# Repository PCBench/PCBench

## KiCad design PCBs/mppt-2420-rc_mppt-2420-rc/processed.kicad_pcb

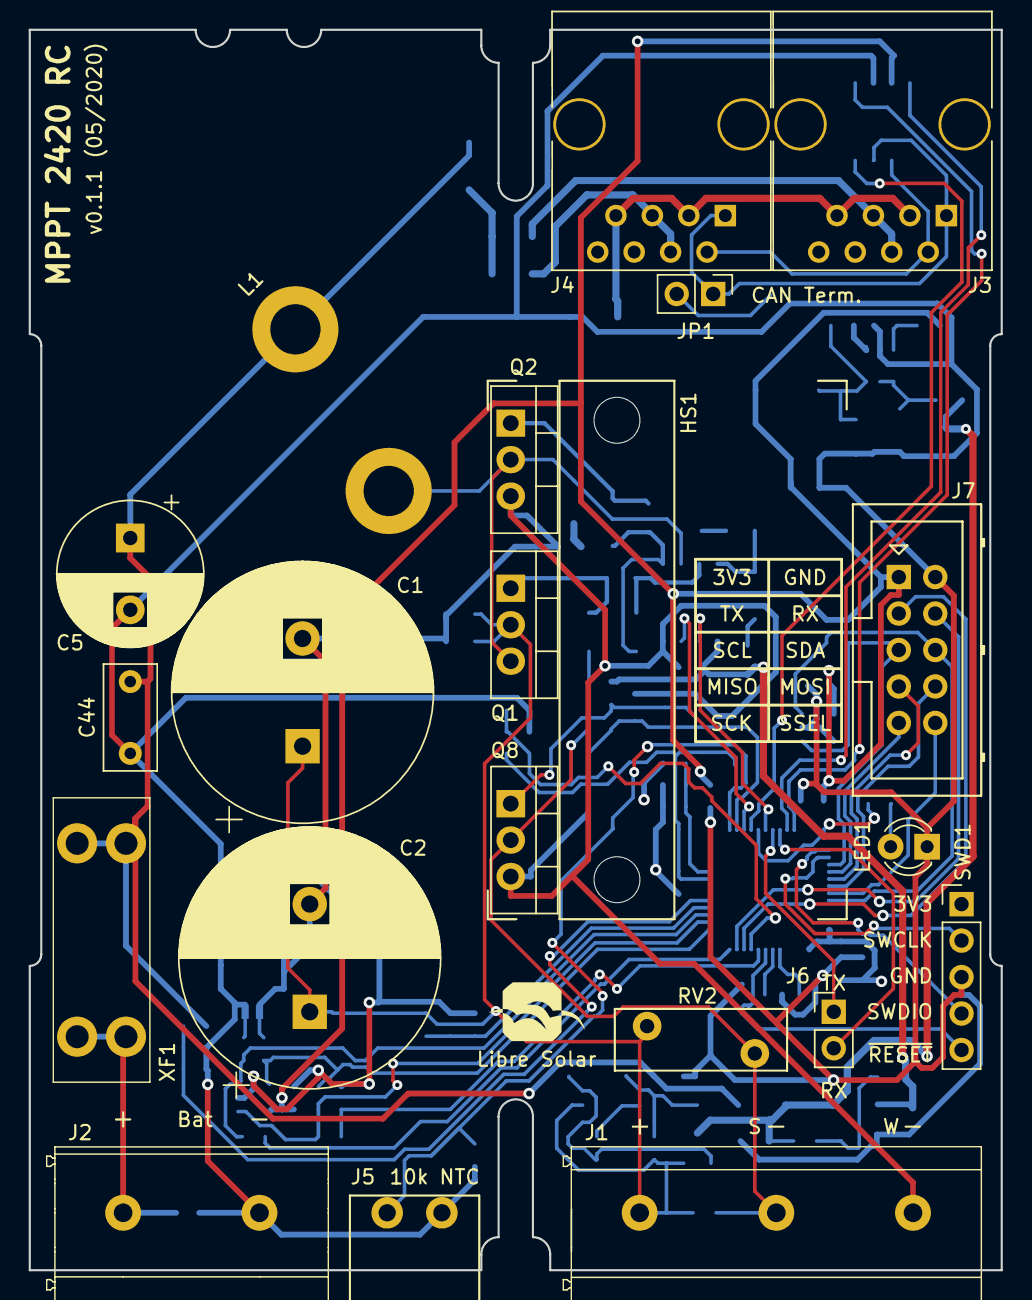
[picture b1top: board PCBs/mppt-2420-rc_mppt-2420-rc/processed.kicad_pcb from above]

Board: 4 copper layers, 67.7 x 86.4 mm, 120 parts (0 on the bottom side), 71 nets.

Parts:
C1, C2: 560µF; CP_Radial_D18.0mm_P7.50mm
C3, C18, C40: 1µF; C_0805_2012
C4: 100nF; C_0805_2012
C5: 820µF; CP_Radial_D10.0mm_P5.00mm
C6, C15: 1nF; C_0603_1608
C7, C9, C10, C11, C20, C22, C29, C30, C31, C32, C36, C48: 100nF; C_0603_1608
C8, C14, C16, C17, C34: 10nF; C_0603_1608
C12, C33, C39, C41, C49: 2.2µF; C_0603_1608
C19: 4.7µF; C_1210_3225
C21, C23: 10µF; C_0805_2012
C44: 0.22µF; C_Rect_L7.2mm_W3.5mm_P5.00mm_FKS2_FKP2_MKS2_MKP2
D1: SS16FP; D_PowerDI-123
D2, D3: NRVTS260ESFT1G; D_SOD-123
D5, D9, D11: 12V; D_SOT-23_ANK
D7, D14, D15: SS14FL; D_SOD-123
D8: 2.5V; D_SOD-123
D10, D16: 1N4148; D_SOD-123
F1: 25A; NULL
F2, F3: 600mA; Fuse_1206_3216Metric
FID1, FID2: Fiducial; Fiducial_0.7mm
HS1: Heatsink; Fischer_Elektronik_SK573_37,5
J1: MKDS 5/ 3-9,5; Phoenix_Contact_MKDS_5-3-9,5
J2: MKDS 5/ 2-9,5; Phoenix_Contact_MKDS_5-2-9,5
J3, J4: 8P8C; RJ45_8P8C
J5: Phoenix Contact MC 1,5; Phoenix_Contact_MC_1,5_2-G-3,81
J6: Conn_01x02; PinHeader_1x02_P2.54mm_Vertical
J7: UEXT; Box_Header_2x05x2.54mm_Straight
JP1: Jumper_NC_Small; PinHeader_1x02_P2.54mm_Vertical
L1: 33µH; L-FERYSTER-DTMSS-27
L2: 4.7µH; L_0805_2012Metric
L3: 47µH; Bourns_SRN6045TA
LED1: red; LED_D3.0mm
LOGO1: LIBRE_SOLAR; LIBRESOLAR_LOGO
LOGO2: OPEN_HARDWARE; OSHW-Logo_5.7x6mm_SilkScreen
NT1, NT2: Net-Tie_2; NetTie-2_SMD_Pad0.5mm
Q1, Q2, Q8: IPP045N10N3G; TO-220-3_Vertical
Q9: DMP10H4D2S; SOT-23
R1, R2, R3, R5: 3R3; R_0805_2012
R4: 2R2; R_1206_3216
R6: 2m; R_Bourns_CRE2512
R7, R24, R39, R41, R45, R64, R65, R66: 10k; R_0603_1608
R8, R10, R14, R20, R21: 2.2k; R_0603_1608
R9, R11: 68k; R_0603_1608
R12: 0R; R_0603_1608
R13, R17: 100k; R_0603_1608
R15, R42: 1k; R_0603_1608
R18: 5.6k; R_0603_1608
R22: 120R; R_1206_3216
R23, R60: 33k; R_0603_1608
R40: 100R; R_0603_1608
R56: 1M; R_0603_1608
RT1: 10k; R_0603_1608
RV2: 82V; RV_Disc_D12mm_W4.3mm_P7.5mm
SWD1: ST_Nucleo_SWD; PinHeader_1x05_P2.54mm_Vertical
T2, T6, T10: MMBT3904; SOT-23
TP4: 12V; TestPoint_Pad_D1.0mm
U1: LM5107; SOIC-8_3.9x4.9mm_Pitch1.27mm
U2: STM32G431CBTx; LQFP-48_7x7mm_P0.5mm
U3: TLV9001; SOT-23-5
U4: LMR16006X; SOT-23-6
U5: TCAN334; SOIC-8_3.9x4.9mm_Pitch1.27mm
U6: 24AA32; SOT-23-5
XF1: ATO blade fuse; Keystone-Fuse-3557-2
Y1: 8MHz; Resonator_Murata_CSTNE

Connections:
+3V3: C7.1, C11.1, C21.1, C22.1, C23.1, C30.1, C31.1, C32.1, C33.1, J7.1, L3.2, R20.2, R21.2, R23.1, R40.2, SWD1.1, U2.1, U2.48, U3.5, U5.3, U6.4
+12V: C12.1, C41.1, R3.2, R12.1, T10.2, TP4.1, U1.1
/BAT+: C8.1, J2.1, XF1.2
/CAN bus/CAN_GND: D3.2, J3.3, J3.7, J4.3, J4.7
/CAN bus/CAN_H: J3.1, J4.1, JP1.1, U5.7
/CAN bus/CAN_L: J3.2, J4.2, R22.2, U5.6
/CAN bus/CAN_RX: U2.33, U5.4
/CAN bus/CAN_STB: U2.28, U5.8
/CAN bus/CAN_TX: U2.34, U5.1
/CAN bus/CAN_V+1: F2.1, J3.4, J3.5
/CAN bus/CAN_V+2: F3.1, J4.4, J4.5
/DC/DC/HS_DRV: D14.1, R1.2, U1.7
/DC/DC/LS_DRV: D7.2, D15.1, R2.2, U1.5
/DC/DC/PWM_HS: U1.2, U2.30
/DC/DC/PWM_LS: U1.3, U2.27
/DC/DC/SHUNT_N: NT1.2, R10.1
/DC/DC/SHUNT_P: NT2.2, R8.1
/DC/DC/SW_NODE: C10.2, L1.1, Q1.3, Q2.2, R4.2, U1.6
/DCDC_HV+: C1.1, C2.1, C3.1, C4.1, C17.1, D11.1, J1.1, Q1.2, Q9.2, R13.1, R60.2, R65.2, RV2.1
/DCDC_HV-: C17.2, J1.2, Q8.2, R41.1, RV2.2
/MCU/ADC1_IN2: C9.1, R7.2, RT1.1, U2.9
/MCU/ADC1_IN11: D8.1, R41.2, T6.1, U2.26
/MCU/ADC1_IN12: C16.1, R17.2, R18.1, U2.17
/MCU/ADC1_IN15: C14.1, R13.2, R14.1, U2.16
/MCU/ADC2_IN1: C15.1, R15.2, U2.8
/MCU/DAC1: R9.1, U2.12
/MCU/I2C1_SCL: J7.5, R20.1, U2.39, U6.1
/MCU/I2C1_SDA: J7.6, R21.1, U2.44, U6.3
/MCU/LED_PWR: R42.2, U2.29
/MCU/OPAMP2_VINM: R10.2, R11.1, U2.13, U3.4
/MCU/OPAMP2_VINP: R8.2, R9.2, U2.15, U3.3
/MCU/OPAMP2_VOUT: R11.2, R15.1, U2.14, U3.1
/MCU/OSC_IN: U2.5, Y1.3
/MCU/OSC_OUT: U2.6, Y1.1
/MCU/SPI1_MISO: J7.7, U2.41
/MCU/SPI1_MOSI: J7.8, U2.42
/MCU/SPI1_SCK: J7.9, U2.40
/MCU/SPI1_SSEL: J7.10, U2.43
/MCU/SWCLK: SWD1.2, U2.38
/MCU/SWDIO: SWD1.4, U2.37
/MCU/TEMP_BAT: C36.1, J5.1, R39.2, U2.25
/MCU/USART1_RX: J6.2, U2.32
/MCU/USART1_TX: J6.1, U2.31
/MCU/USART2_RX: J7.4, U2.11
/MCU/USART2_TX: J7.3, U2.10
/MCU/~RESET: C29.1, SWD1.5, U2.7
/Power Supply/SMPS_SUPPLY: C18.1, C40.1, D10.1, L2.1, Q9.3, R64.2, T10.3
GND: C5.2, C7.2, C8.2, C9.2, C11.2, C14.2, C15.2, C16.2, C18.2, C19.2, C21.2, C22.2, C23.2, C29.2, C30.2, C31.2, C32.2, C33.2, C34.2, C36.2, C39.2, C40.2, C41.2, C44.1, C48.2, C49.2, D1.2, D3.1, D5.2, D9.2, J2.2, J5.2, J7.2, LED1.1, NT2.1, R6.1, R14.2, R18.2, R24.2, RT1.2, SWD1.3, U3.2, U4.2, U5.2, U6.2, U6.5, Y1.2
GNDPWR: C1.2, C2.2, C3.2, C4.2, C6.2, C12.2, D8.2, J1.3, NT1.1, Q2.3, Q8.3, R6.2, R56.2, T6.2, U1.4
unnamed: C6.1, R4.1
unnamed: C10.1, R5.2
unnamed: C19.1, L2.2, U4.4, U4.5
unnamed: C20.1, U4.1
unnamed: C20.2, D1.1, L3.1, U4.6
unnamed: D2.1, F2.2, F3.2
unnamed: D5.1, R64.1, T10.1
unnamed: D7.1, R12.2, R45.1
unnamed: D9.1, R60.1, T2.1
unnamed: D11.2, Q9.1, R65.1, R66.2
unnamed: D14.2, Q1.1, R1.1
unnamed: D15.2, Q2.1, R2.1
unnamed: D16.1, R5.1, U1.8
unnamed: D16.2, R3.1
unnamed: JP1.2, R22.1
unnamed: LED1.2, R42.1
unnamed: Q8.1, R45.2, R56.1, T6.3
unnamed: R23.2, R24.1, U4.3
unnamed: R66.1, T2.3
VBUS: C5.1, C44.2, D2.2, D10.2, L1.2, R17.1, T2.2, XF1.1
VDDA: C34.1, C39.1, R40.1, U2.21
VREF: C48.1, C49.1, R7.1, R39.1, U2.20

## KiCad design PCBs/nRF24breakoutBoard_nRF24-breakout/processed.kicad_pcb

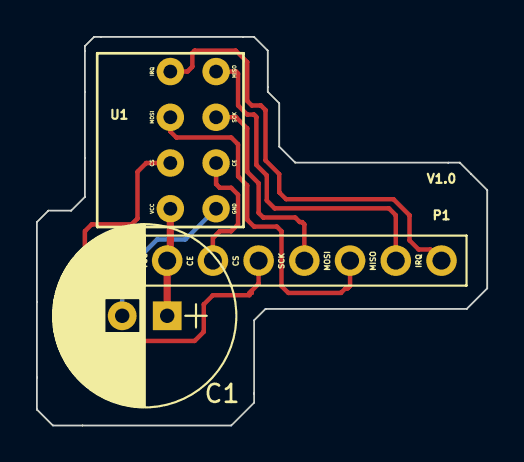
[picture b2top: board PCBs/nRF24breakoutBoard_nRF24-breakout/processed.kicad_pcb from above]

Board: 2 copper layers, 25.0 x 21.6 mm, 3 parts (0 on the bottom side), 8 nets.

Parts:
C1: 10uF; CP_Radial_D10.0mm_P2.50mm
P1: CONN_01X08; Pin_Header_Straight_1x08_Pitch2.54mm
U1: nRF24

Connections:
unnamed: C1.1, P1.2, U1.2
unnamed: C1.2, P1.1, U1.1
unnamed: P1.3, U1.3
unnamed: P1.4, U1.4
unnamed: P1.5, U1.5
unnamed: P1.6, U1.6
unnamed: P1.7, U1.7
unnamed: P1.8, U1.8

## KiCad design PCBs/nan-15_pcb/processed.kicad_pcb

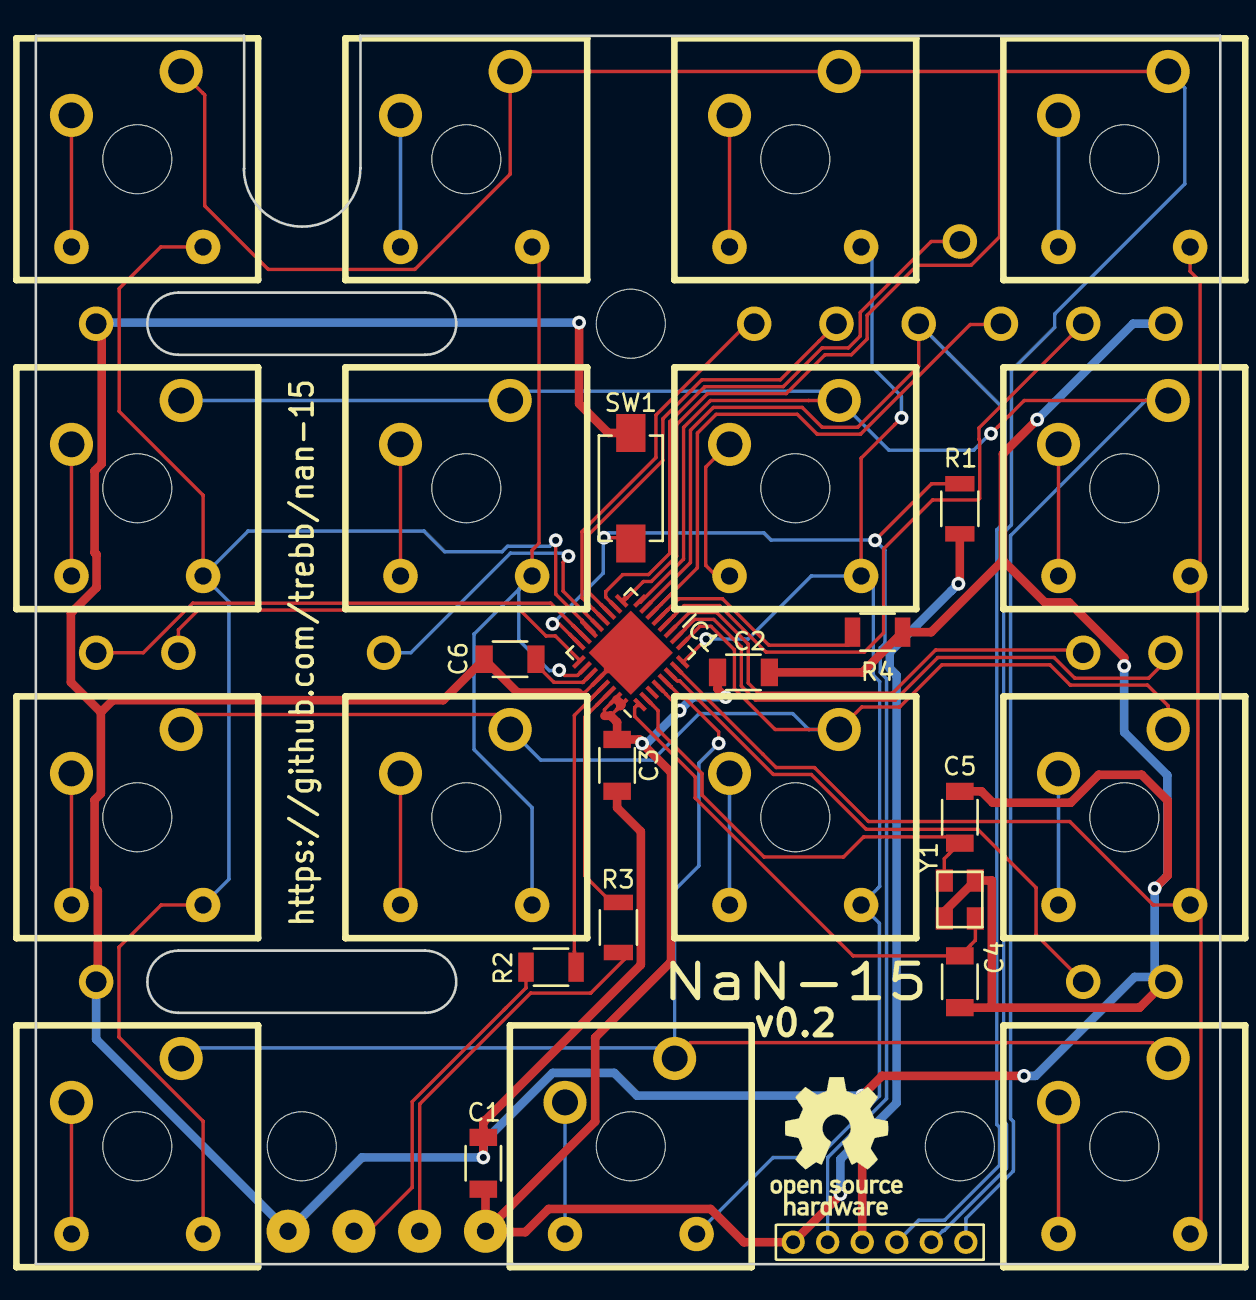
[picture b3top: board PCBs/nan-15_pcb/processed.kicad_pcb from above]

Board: 2 copper layers, 68.6 x 71.1 mm, 50 parts (1 on the bottom side), 46 nets.

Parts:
C1, C6: 1u; C_1206
C2, C3: 100n; C_1206
C4, C5: 18p; C_1206
HS1, HS2, HS3: HEATSINK; Plain_Hole_4mm
IC1: ATMEGA32U2; QFN-32-1EP_5x5mm_Pitch0.5mm
OSHW: OSHW-Logo_28.5x30mm_SilkScreen
P1: USB; SolderWirePad_4xInline_1mmDrill
P2: PRGM; Program_1x06
R1, R4: 10k; R_1206
R2, R3: 22; R_1206
SW1: SW_PUSH; button_3x6_smd
U00, U01, U02, U03, U10, U11, U12, U13, U20, U21, U22, U23, U30, U32, U33: MX-DI; MXDIODE
W0, W1, W2, W3, W4, W5, W6, W7, W8, W9, W10, W11, W50, W51, W52, W53: TEST_1P; SolderWirePad_2mm_1-2mmDrill_no_legend
Y1: MT 16MHz; crystal_MT_32x25

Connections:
/D+: IC1.29, R2.1
/D-: IC1.30, R3.1
/col0: IC1.22, U00.4, U10.4, U20.4, U30.4
/col1: IC1.26, U01.4, U11.4, U21.4
/col2: IC1.8, U02.4, U12.4, U22.4, U32.4
/col3: IC1.7, U03.4, U13.4, U23.4, U33.4
/led0: IC1.6, W0.1
/led1: IC1.10, W1.1
/led2: IC1.11, W2.1
/led3: IC1.12, W3.1
/led4: IC1.14, W4.1
/led5: IC1.15, P2.3, W5.1
/led6: IC1.18, W6.1
/led7: IC1.19, W7.1
/led8: IC1.20, W8.1
/led9: IC1.21, W9.1
/led10: IC1.25, W10.1
/led11: IC1.23, W11.1
/row0: IC1.17, P2.2, U00.2, U01.2, U02.2, U03.2
/row1: IC1.16, P2.1, U10.2, U11.2, U12.2, U13.2
/row2: IC1.9, U20.2, U21.2, U22.2, U23.2
/row3: IC1.5, U30.2, U32.2, U33.2
GND: C1.2, C2.2, C3.2, C4.2, C5.2, C6.1, IC1.28, IC1.33, P1.5, P2.4, R4.1, SW1.1, W50.1, W51.1, W52.1, W53.1, Y1.3
unnamed: C4.1, IC1.1
unnamed: C5.1, IC1.2
unnamed: C6.2, IC1.27
unnamed: IC1.13, R4.2
unnamed: IC1.24, P2.5, R1.2, SW1.2
unnamed: P1.2, R3.2
unnamed: P1.3, R2.2
unnamed: U00.1, U00.3
unnamed: U01.1, U01.3
unnamed: U02.1, U02.3
unnamed: U03.1, U03.3
unnamed: U10.1, U10.3
unnamed: U11.1, U11.3
unnamed: U12.1, U12.3
unnamed: U13.1, U13.3
unnamed: U20.1, U20.3
unnamed: U21.1, U21.3
unnamed: U22.1, U22.3
unnamed: U23.1, U23.3
unnamed: U30.1, U30.3
unnamed: U32.1, U32.3
unnamed: U33.1, U33.3
VCC: C1.1, C2.1, C3.1, IC1.4, IC1.31, IC1.32, P1.1, P2.6, R1.1

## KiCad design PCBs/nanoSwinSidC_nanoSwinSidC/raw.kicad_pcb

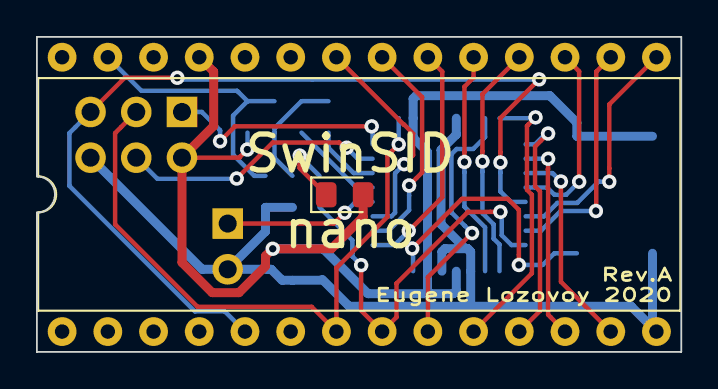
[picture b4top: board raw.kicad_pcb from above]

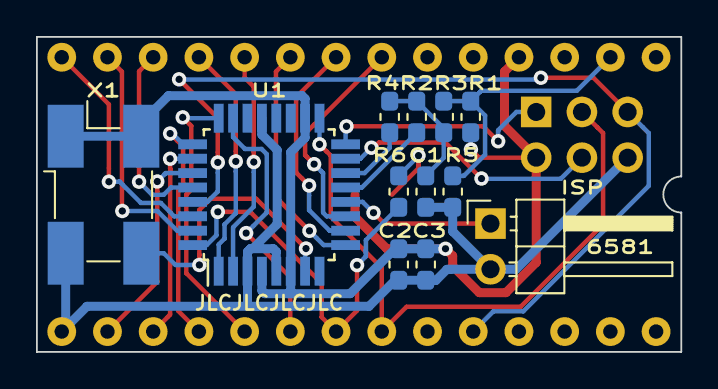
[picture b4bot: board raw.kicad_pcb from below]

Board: 2 copper layers, 35.8 x 17.5 mm, 15 parts (12 on the bottom side), 27 nets.

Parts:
C1: 470p; C_0603_1608Metric_Pad1.05x0.95mm_HandSolder
C2: 100n; C_0603_1608Metric_Pad1.05x0.95mm_HandSolder
C3: 10n; C_0603_1608Metric_Pad1.05x0.95mm_HandSolder
D1: LED; LED_0805_2012Metric_Pad1.15x1.40mm_HandSolder
J1: Conn_02x03_Odd_Even; PinHeader_2x03_P2.54mm_Vertical
J2: Conn_02x14_Counter_Clockwise; DIP-28_W15.24mm
JP1: Jumper; PinHeader_1x02_P2.54mm_Horizontal
R1: 4.7k; R_0603_1608Metric_Pad1.05x0.95mm_HandSolder
R2, R5, R6: 1k; R_0603_1608Metric_Pad1.05x0.95mm_HandSolder
R3: 2.2k; R_0603_1608Metric_Pad1.05x0.95mm_HandSolder
R4: 240k; R_0603_1608Metric_Pad1.05x0.95mm_HandSolder
U1: ATmega88PA-AU; TQFP-32_7x7mm_P0.8mm
X1: 32 MHz; Oscillator_SMD_EuroQuartz_XO91-4Pin_7.0x5.0mm_HandSoldering

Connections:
+5V: C2.1, C3.1, D1.2, J1.2, J2.25, R1.1, U1.4, U1.6, U1.18, X1.1, X1.4
A0: J2.9, U1.23
A1: J2.10, U1.24
A2: J2.11, U1.25
A3: J2.12, U1.26
A4: J2.13, U1.27
D0: J2.15, U1.30
D1: J2.16, U1.31
D2: J2.17, U1.28
D3: J2.18, U1.1
D4: J2.19, U1.2
D5: J2.20, U1.9
D6: J2.21, U1.10
D7: J2.22, U1.11
GND: C1.2, C2.2, C3.2, J1.6, J2.14, JP1.2, R5.2, U1.3, U1.5, U1.21, X1.2
MISO: J1.1, U1.16
MOSI: J1.4, U1.15
unnamed: C1.1, R2.1, R3.2, R4.1
unnamed: D1.1, R6.1
unnamed: JP1.1, U1.12
unnamed: R2.2, U1.13
unnamed: R4.2, U1.14
unnamed: U1.7, X1.3
SCK: J1.3, J2.7, U1.17
SND: J2.27, R1.2, R3.1, R5.1
nCS: J2.8, R6.2, U1.32
nRST: J1.5, J2.5, U1.29

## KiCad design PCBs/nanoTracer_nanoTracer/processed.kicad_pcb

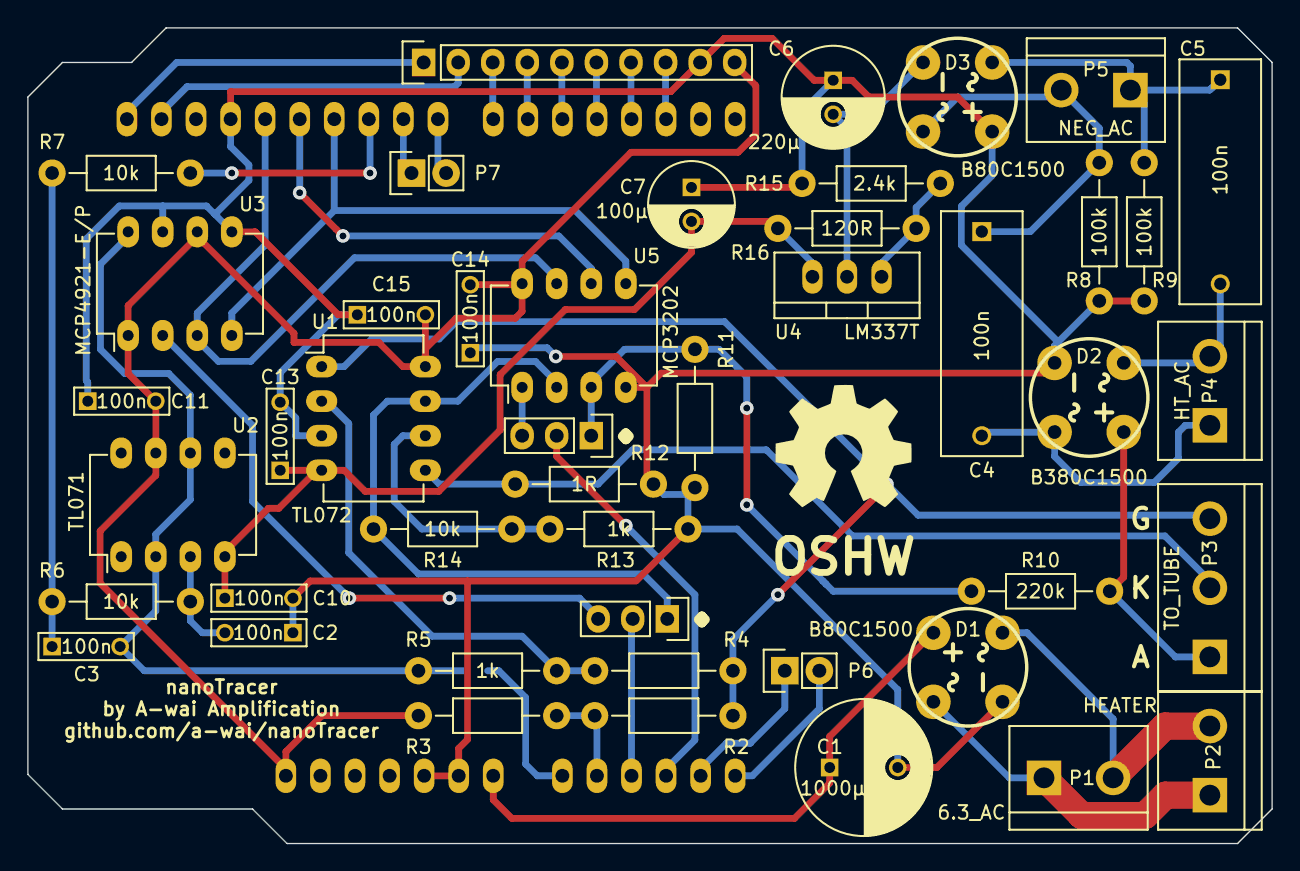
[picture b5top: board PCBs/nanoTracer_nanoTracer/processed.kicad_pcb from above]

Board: 2 copper layers, 91.4 x 59.9 mm, 48 parts (0 on the bottom side), 44 nets.

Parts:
C1: 1000µ; C_Radial_D10_L16_P5
C2, C3, C10, C11, C13, C14, C15: 100n; C_Rect_L7_W2_P5
C4, C5: 100n; C_Rect_L18_W6_H12_P15
C6: 220µ; C_Radial_D7.5_L11.2_P2.5
C7: 100µ; C_Radial_D6.3_L11.2_P2.5
D1, D3: B80C1500; bridge_wob
D2: B380C1500; bridge_wob
J1: SIL10; Pin_Header_Straight_1x10
JP1, JP2: JUMPER3; Pin_Header_Straight_1x03
JP3: JUMPER; SJ_OPEN
LOGO_OSHW_silkscreen_10mm: val**; LOGO_OSHW_silkscreen_10mm
P1: 6.3_AC; bornier2
P2: HEATER; bornier2
P3: TO_TUBE; bornier3
P4: HT_AC; bornier2
P5: NEG_AC; bornier2
P6, P7: CONN_2; Pin_Header_Straight_1x02
R2: R2; Resistor_Horizontal_RM10mm
R3: R3; Resistor_Horizontal_RM10mm
R4: R4; Resistor_Horizontal_RM10mm
R5, R13: 1k; Resistor_Horizontal_RM10mm
R6, R7, R14: 10k; Resistor_Horizontal_RM10mm
R8, R9: 100k; Resistor_Horizontal_RM10mm
R10: 220k; Resistor_Horizontal_RM10mm
R11: R11; Resistor_Horizontal_RM10mm
R12: 1R; Resistor_Horizontal_RM10mm
R15: 2.4k; Resistor_Horizontal_RM10mm
R16: 120R; Resistor_Horizontal_RM10mm
SHIELD1: ARDUINO_SHIELD
U1: TL072; DIP-8_W7.62mm_LongPads
U2: TL071; DIP-8_W7.62mm_LongPads
U3: MCP4921-E/P; DIP-8_W7.62mm_LongPads
U4: LM337T; TO-220_Neutral123_Vertical
U5: MCP3202; DIP-8_W7.62mm_LongPads

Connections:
/CS_ADC: JP1.3, U5.1
/CS_DAC: JP2.3, U3.2
/D8: P7.2, SHIELD1.8
/D9: P7.1, SHIELD1.9
/DAC_OUT: C3.2, JP3.1, R5.1, U2.2, U2.6, U3.8
/GRID: P3.3, R2.2, R4.2, U1.1
/IA: JP2.1, R14.1, U1.7, U5.2
/LCD_D4: J1.6, SHIELD1.4
/LCD_D5: J1.5, SHIELD1.5
/LCD_D6: J1.4, SHIELD1.6
/LCD_D7: J1.3, SHIELD1.7
/LCD_EN: J1.7, SHIELD1.3
/LCD_RS: J1.8, SHIELD1.2
/MISO: SHIELD1.12, U5.6
/MOSI: SHIELD1.11, U3.4, U5.5
/PWM_OUT: R7.1, SHIELD1.10
/SCK: SHIELD1.13, U3.3, U5.7
/SCL: J1.1, SHIELD1.SCL
/SDA: J1.2, SHIELD1.SDA
/UA: JP1.1, R10.2, R11.1, U5.3
/UG: R2.1, R3.2, SHIELD1.AD1
/UK: P3.2, R12.1, U1.5
/VIN: C1.1, D1.3, SHIELD1.V_IN
A+: D2.3, P3.1, R10.1
GND: C1.2, C2.1, C6.1, C7.1, C10.2, C11.1, C13.2, C14.1, C15.1, D1.1, D2.1, D3.3, J1.9, R8.1, R9.1, R11.2, R12.2, R13.1, R15.1, SHIELD1.GND1, SHIELD1.GND2, SHIELD1.GND3, U1.3, U3.5, U3.7, U5.4
unnamed: C2.2, R6.2, U2.3
unnamed: C3.1, R6.1, R7.2
unnamed: C4.1, D3.4, P5.2, R8.2
unnamed: C4.2, D2.4, P4.1
unnamed: C5.1, D3.2, P5.1, R9.2
unnamed: C5.2, D2.2, P4.2
unnamed: C6.2, D3.1, U4.2
unnamed: D1.2, P1.1, P2.1
unnamed: D1.4, P1.2, P2.2
unnamed: JP1.2, SHIELD1.AD3
unnamed: JP2.2, SHIELD1.AD2
unnamed: JP3.2, SHIELD1.AD0
unnamed: P6.1, SHIELD1.AD4
unnamed: P6.2, SHIELD1.AD5
unnamed: R4.1, R5.2, U1.2
unnamed: R13.2, R14.2, U1.6
unnamed: R15.2, R16.1, U4.1
VDD: C11.2, C14.2, C15.2, J1.10, R3.1, SHIELD1.IO_R, U1.8, U2.7, U3.1, U3.6, U5.8
VSS: C7.2, C10.1, C13.1, R16.2, U1.4, U2.4, U4.3

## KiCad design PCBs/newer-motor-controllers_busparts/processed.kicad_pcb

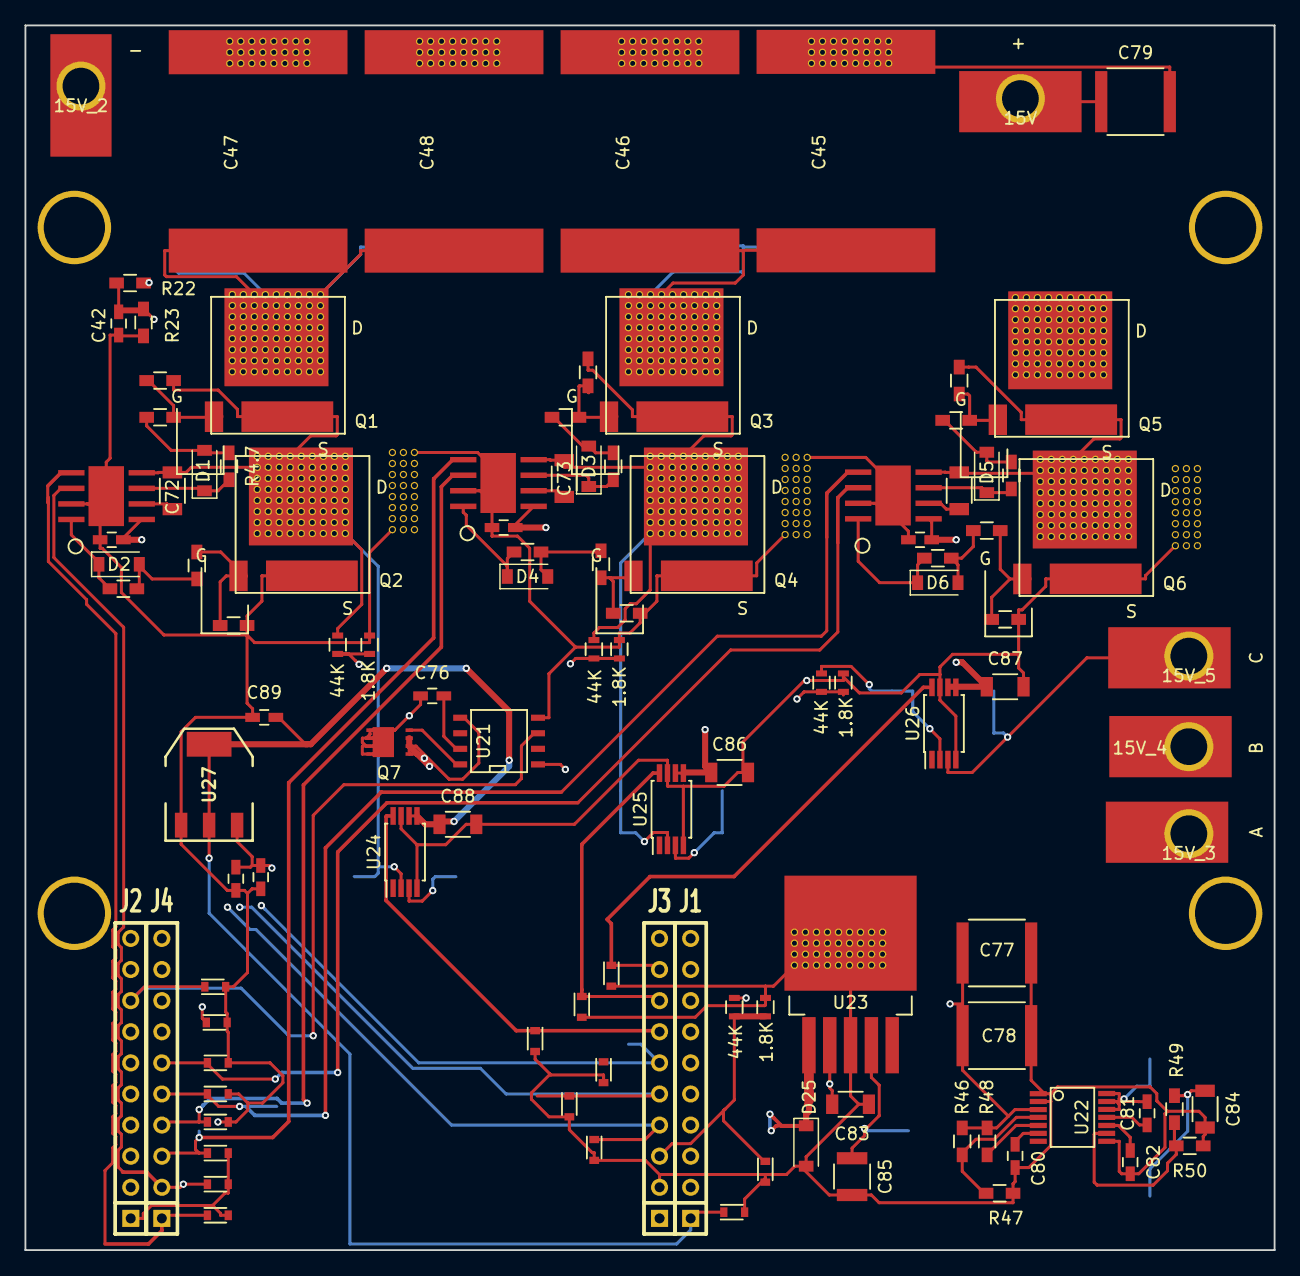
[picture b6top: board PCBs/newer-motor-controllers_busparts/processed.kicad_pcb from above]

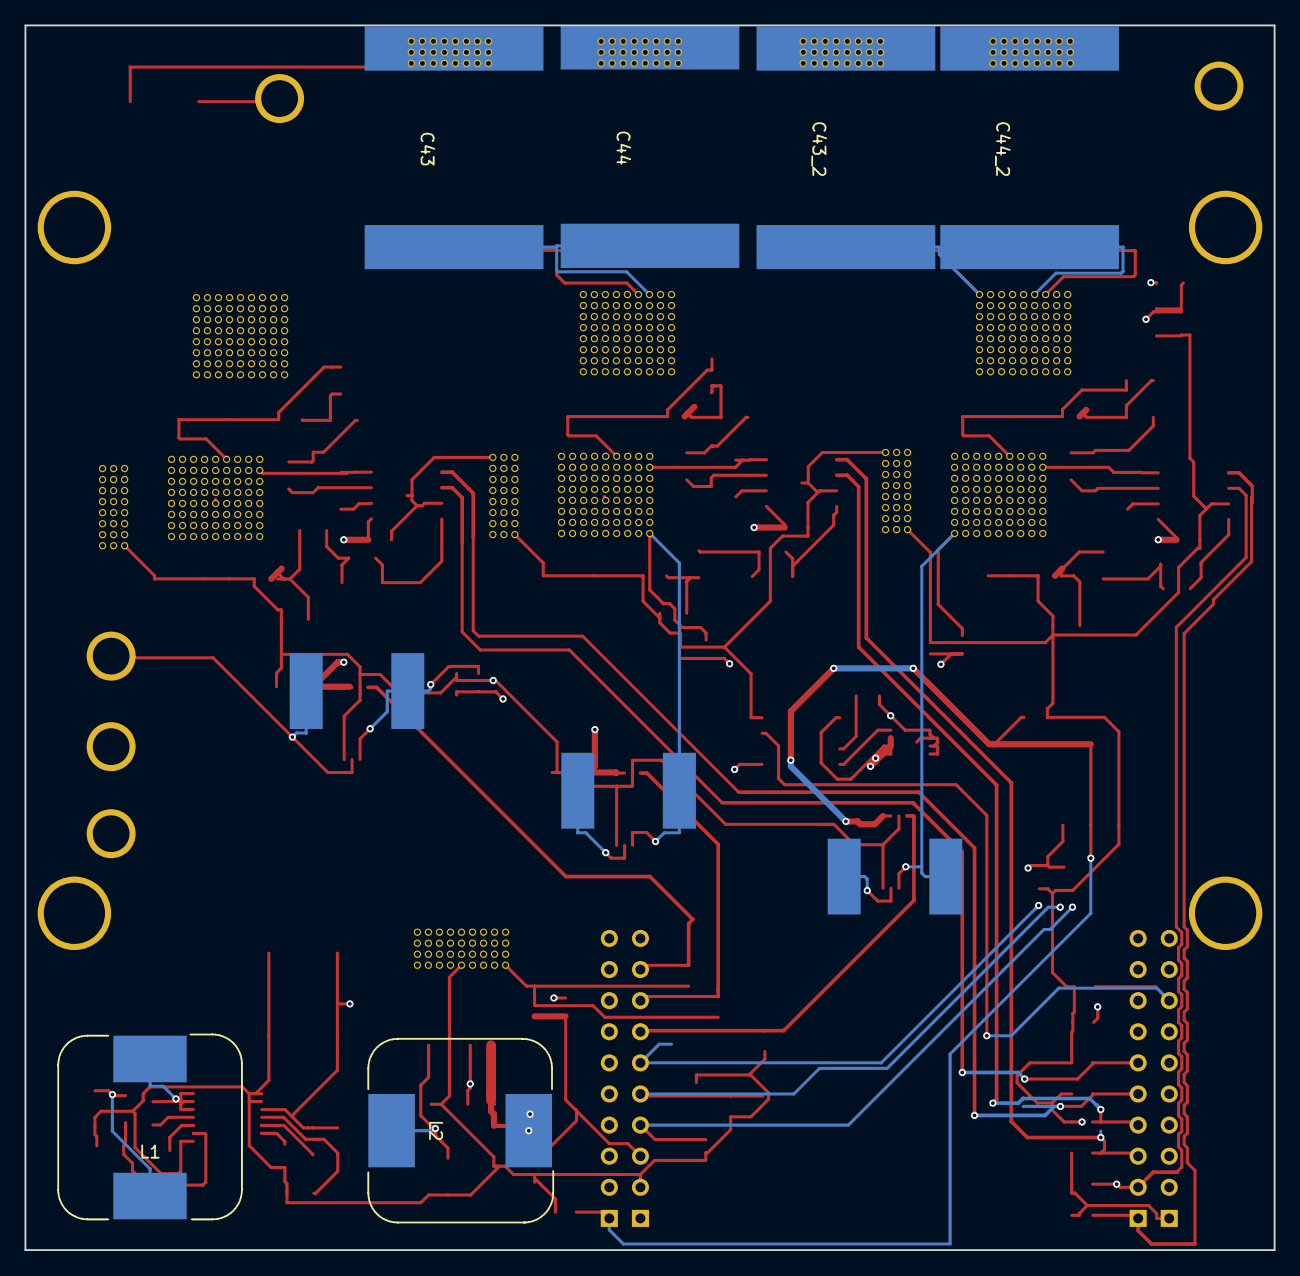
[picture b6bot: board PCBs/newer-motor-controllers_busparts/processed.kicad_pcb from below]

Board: 4 copper layers, 102.0 x 100.0 mm, 123 parts (9 on the bottom side), 58 nets.

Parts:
10k1, 10k2, 10k3, 10k4, 10k5, 10k6: R_Small; R_0603_HandSoldering
15V, 15V_2, 15V_3, 15V_4, 15V_5: via
+: V+; SolderWirePad_single_SMD_5x10mm
-: V-; SolderWirePad_single_SMD_5x10mm
A: motor_A; SolderWirePad_single_SMD_5x10mm
B: motor_B; SolderWirePad_single_SMD_5x10mm
C: motor_C; SolderWirePad_single_SMD_5x10mm
C42: 2.2uf; C_0603_HandSoldering
C43, C43_2, C44, C44_2, C45, C46, C47, C48: 4.7uf; cap_6065
C69, C70, C71, C82, C89: 1uf; C_0603_HandSoldering
C72, C73, C74, C86, C87, C88: 0.1uf; C_1206
C75: 0.1uf; C_0603_HandSoldering
C76: 10pf; C_0603_HandSoldering
C77, C78, C79: 1uf 250V; C_2220
C80: 22nf; C_0603_HandSoldering
C81: 10nf; C_0603_HandSoldering
C83, C84: 10uf; C_1206
C85: 100uf; C_1210
C90: 10uf; C_0603_HandSoldering
D1, D2, D3, D4, D5, D6: D_Schottky_Small; SOD-123
D8, D9, D10, D11, D12, D13, D14, D15, D16, D17, D18, D19, D20, D21, D22, D23: TVS; D_0603
D25: D_Schottky; SOD-123
J1: Ti_Booster_40_J1; SIL-10J1
J2: Ti_Booster_40_J2; SIL-10J2
J3: Ti_Booster_40_J3; SIL-10J3
J4: Ti_Booster_40_J4; SIL-10J4
L1, L2: INDUCTOR; MSS1583-154KED
Q1, Q2, Q3, Q4, Q5, Q6: FDMT-800; P-PG-HSOF-08
Q7: Q_NMOS_DSG; VSONP-8
R4.1, R4.2, R4.3, R4.4, R4.5, R4.7: R_Small; R_0603_HandSoldering
R22: NTC 10k; R_0603_HandSoldering
R23: 10k; R_0603_HandSoldering
R40, R41, R42, R42_2: 1.8K; R_0603
R43, R44, R45, R45_2: 44K; R_0603
R46: 75k; R_0603_HandSoldering
R47: 4.42k; R_0603_HandSoldering
R48: 499k; R_0603_HandSoldering
R49: 13k; R_0603_HandSoldering
R50: 2k; R_0603_HandSoldering
R51, R52, R53: 0.001R; SHUNT_CSS2H-3920
U18, U19, U20: UCC27210; SO_PowerPAD-8
U21: Si8751; SOIC-8-N
U22: LM5161; SSOP-14
U23: LM2595; TO-263-5Lead
U24, U25, U26: INA240; TSSOP-8_4.4x3mm_Pitch0.65mm
U27: NCP1117ST33T3G; SOT-223
ferrite1, ferrite2, ferrite3, ferrite4, ferrite5, ferrite6: R_Small; R_0603_HandSoldering

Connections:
+5V: C75.1, C85.1, C90.1, J3.1, L2.2, U21.1, U23.4, U27.3
+15V: C76.1, C83.1, C84.1, L1.2, Q7.1, R49.1, U23.2
/Ti_120vgate/vsense_a: D12.1, J3.4, R40.2, R43.2
/Ti_120vgate/vsense_b: D13.1, J3.5, R41.2, R44.2
/Ti_120vgate/vsense_c: J3.6, R42.2, R45.2
/VBUS: 15V.1, +.1, C43.2, C43_2.2, C44.2, C44_2.2, C45.2, C46.2, C47.2, C48.2, C77.1, C78.1, C79.1, Q1.1, Q3.1, Q5.1, R45_2.1, R46.1, R48.2, U22.3
/connector/CurrentA: D15.1, J3.7, U24.8
/connector/CurrentB: D16.1, J3.8, U25.8
/connector/CurrentC: D17.1, J3.9, U26.8
/connector/EN_GATE: D10.1, J2.8, U21.3
/connector/PWM_H1: D18.1, J4.1, U18.5
/connector/PWM_H2: D20.1, J4.3, U19.5
/connector/PWM_H3: D22.1, J4.5, U20.5
/connector/PWM_L1: D19.1, J4.2, U18.6
/connector/PWM_L2: D21.1, J4.4, U19.6
/connector/PWM_L3: D23.1, J4.6, U20.6
/connector/TEMP: C42.1, D8.1, J2.3, R22.2, R23.1
/connector/VBUS_sense: D11.1, J3.3, R42_2.2, R45_2.2
/current_sense_80v/PHASE_1: 15V_3.1, A.1, R53.1, U24.3
/current_sense_80v/PHASE_2: 15V_4.1, B.1, R52.1, U25.3
/current_sense_80v/PHASE_3: 15V_5.1, C.1, R51.1, U26.3
/mosfet/H1: D1.1, R4.7.2, U18.3
/mosfet/H2: D3.1, R4.2.2, U19.3
/mosfet/H3: D5.1, R4.4.2, U20.3
/mosfet/L1: D2.1, R4.1.2, U18.8
/mosfet/L2: D4.1, R4.3.2, U19.8
/mosfet/L3: D6.1, R4.5.2, U20.8
/mosfet/phase_a_in: 10k1.2, C72.1, Q1.2, Q2.1, R43.1, R53.2, U18.4, U24.2
/mosfet/phase_b_in: 10k3.2, C73.1, Q3.2, Q4.1, R44.1, R52.2, U19.4, U25.2
/mosfet/phase_c_in: 10k5.2, C74.1, Q5.2, Q6.1, R45.1, R51.2, U20.4, U26.2
GND: 10k2.2, 10k4.2, 10k6.2, 15V_2.1, -.1, C42.2, C43.1, C43_2.1, C44.1, C44_2.1, C45.1, C46.1, C47.1, C48.1, C69.2, C70.2, C71.2, C75.2, C77.2, C78.2, C79.2, C80.2, C82.2, C83.2, C84.2, C85.2, C86.2, C87.2, C88.2, C89.2, C90.2, D8.2, D9.2, D10.2, D11.2, D12.2, D13.2, D14.2, D15.2, D16.2, D17.2, D18.2, D19.2, D20.2, D21.2, D22.2, D23.2, D25.2, J2.1, J3.2, Q2.2, Q4.2, Q6.2, R23.2, R40.1, R41.1, R42.1, R42_2.1, R47.2, R50.2, U18.7, U18.pad, U19.7, U19.pad, U20.7, U20.pad, U21.4, U22.1, U22.2, U22.8, U23.3, U24.4, U24.7, U25.4, U25.7, U26.4, U26.7, U27.1
unnamed: 10k1.1, Q1.3, ferrite1.1
unnamed: 10k2.1, Q2.3, ferrite2.1
unnamed: 10k3.1, Q3.3, ferrite3.1
unnamed: 10k4.1, Q4.3, ferrite4.1
unnamed: 10k5.1, Q5.3, ferrite5.1
unnamed: 10k6.1, Q6.3, ferrite6.1
unnamed: C69.1, C70.1, C71.1, Q7.2, U18.1, U19.1, U20.1, U21.5
unnamed: C72.2, U18.2
unnamed: C73.2, U19.2
unnamed: C74.2, U20.2
unnamed: C76.2, U21.7
unnamed: C80.1, U22.6
unnamed: C81.1, L1.1, U22.12, U22.13, U22.14
unnamed: C81.2, U22.11
unnamed: C82.1, U22.10
unnamed: C86.1, C87.1, C88.1, C89.1, D9.1, J1.1, R22.1, U24.5, U24.6, U25.5, U25.6, U26.5, U26.6, U27.2
unnamed: D1.2, R4.7.1, ferrite1.2
unnamed: D2.2, R4.1.1, ferrite2.2
unnamed: D3.2, R4.2.1, ferrite3.2
unnamed: D4.2, R4.3.1, ferrite4.2
unnamed: D5.2, R4.4.1, ferrite5.2
unnamed: D6.2, R4.5.1, ferrite6.2
unnamed: D25.1, L2.1, U23.1
unnamed: Q7.3, U21.8
unnamed: R46.2, R47.1, U22.4
unnamed: R48.1, U22.5
unnamed: R49.2, R50.1, U22.9

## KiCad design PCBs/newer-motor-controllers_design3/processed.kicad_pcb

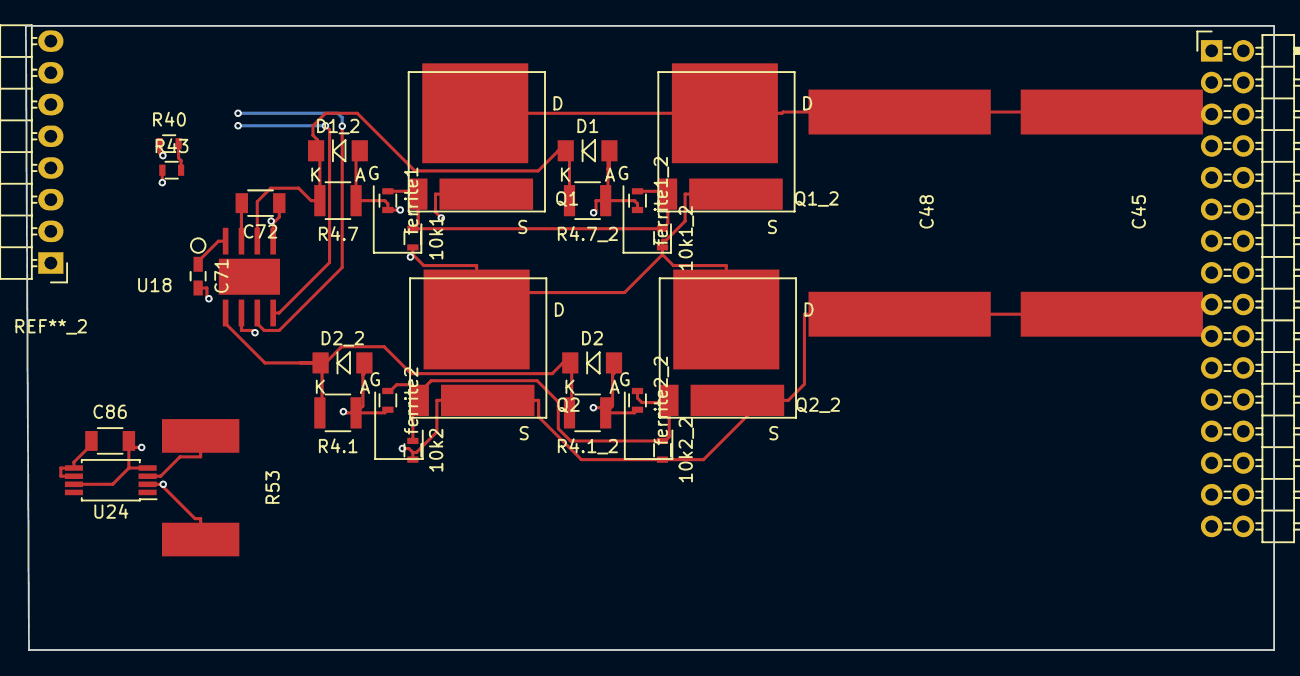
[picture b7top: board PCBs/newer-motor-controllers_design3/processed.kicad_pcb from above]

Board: 4 copper layers, 100.0 x 50.0 mm, 30 parts (0 on the bottom side), 14 nets.

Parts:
10k1, 10k1_2, 10k2, 10k2_2: R_Small; R_0603
C45, C48: 4.7uf; cap_6065
C71: 1uf; C_0603_HandSoldering
C72, C86: 0.1uf; C_1206
D1, D1_2, D2, D2_2: D_Schottky_Small; MiniMELF_Standard
Q1, Q1_2, Q2, Q2_2: FDMT-800; P-PG-HSOF-08
R4.1, R4.1_2, R4.7, R4.7_2: R_Small; R_1210
R40: 1.8K; R_0603
R43: 39K; R_0603
R53: 0.001R; SHUNT_CSS2H-3920
U18: UCC27210; SO_PowerPAD-8
U24: INA240; TSSOP-8_4.4x3mm_Pitch0.65mm
ferrite1, ferrite1_2, ferrite2, ferrite2_2: R_Small; R_0603

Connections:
/Ti_120vgate/H1: D1.1, D1_2.1, R4.7.2, R4.7_2.2, U18.3
/Ti_120vgate/L1: D2.1, D2_2.1, R4.1.2, R4.1_2.2, U18.8
/Ti_120vgate/phase_a_in: 10k1.2, 10k1_2.2, C72.1, Q1.2, Q1_2.2, Q2.1, Q2_2.1, R43.1, R53.2, U18.4, U24.2
/connector/Vsense_a: R40.2, R43.2
/mosfet/VBUS: C45.2, C48.2, Q1.1, Q1_2.1
GND: 10k2.2, 10k2_2.2, C45.1, C48.1, C71.2, C86.2, Q2.2, Q2_2.2, R40.1, U18.7, U24.4, U24.7
unnamed: 10k1.1, 10k1_2.1, Q1.3, Q1_2.3, ferrite1.1, ferrite1_2.1
unnamed: 10k2.1, 10k2_2.1, Q2.3, Q2_2.3, ferrite2.1, ferrite2_2.1
unnamed: C71.1, U18.1
unnamed: C72.2, U18.2
unnamed: C86.1, U24.5, U24.6
unnamed: D1.2, D1_2.2, R4.7.1, R4.7_2.1, ferrite1.2, ferrite1_2.2
unnamed: D2.2, D2_2.2, R4.1.1, R4.1_2.1, ferrite2.2, ferrite2_2.2
unnamed: R53.1, U24.3
